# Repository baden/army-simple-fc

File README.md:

## Планую розробити власний контролер автопілота та польотний контролер.

## Розподілення каналів.

Канал | Де на пульті | Призначення
:-----:|:--------:|:------
1 | Ail правий стік вліво-вправо  | Повертання та разворот на місці 
2 | Ele правий стік донизу-догори | Рух вперед-назад
3 | Thr лівий стік донизу-догори  | Керування газом двигуна
4 | Rud лівий стік вліво-вправо   | Не задіян
5 | SA Арм/Дісарм (лівий двохпозиційний стік)  | Дозвіл на керування. При вимиканні зупиняє рух та вимикає двигун
6 | лівий трьохпозиційний стік | Не задіян
7 | правий трьохпозиційний стік | Не задіян
8 | правий двохпозиційний стік | Не задіян
9 | Назначається на нижню кнопку зліва, без фіксації | Глушення мотору, або декомпресор для старту
10 | Назначається на середню кнопку зліва, без фіксації | Стартер
11 | Назначається на верхню кнопку зліва, з фіксацією | Дозвіл на запуск двигуна. Не під'єднан.
12 | Назначається на верхню та нижню кнопки з правої сторони. | Керування лебідкою.
13 |
14 |
15 |
16 |

## Звукові сигнали

При подачі живлення видається короткий звуковий сигнал.
При підключенні до пульта видається другий звуковий сигнал.
При активації ARM видається третій звуковий сигнал.
При диактивації ARM видається два звукових сигнала.
При втачанні звʼязку з пультом видається три звукових сигнала.
При втрачанні звʼязку більше ніж на хвилину, видається три довгих звукових сигнали.

# Нахрін ZephyrOS. Все шо далі не читайте. Може колись повернусь.

# По ПО.

## Налаштування робочого оточення

Я використовую (коли згадую) оце: [uv](https://github.com/astral-sh/uv)
Але зі звичайним python/pip це працює точнісенько так само.

```
uv venv --python 3.12
source .venv/bin/activate
uv pip install west

cd zephyrproject
west init -l army-simple-fc
west update
uv pip install -r zephyr/scripts/requirements.txt
#west config --global zephyr.base-prefer configfile
west zephyr-export
west build -s army-simple-fc -p -b army_simple_fc_v1_0

```

Збірка

```
west build -s army-simple-fc -p -b army_simple_fc_v1_0
```

Це вже не актуально:

```
uv venv --python 3.12
source .venv/bin/activate
uv pip install west
west init -m https://github.com/baden/fxa-custom-zephyr --mr main zephyrproject
cd zephyrproject
west update
west zephyr-export
uv pip install -r zephyr/scripts/requirements.txt
```

Напевно ще треба зробити 

```
cd zephyr
west sdk install
```

але я поки не хочу, бо це довго і багато буде качати

Пробуємо шось зібрати

```
west build -p always -b nucleo_g070rb zephyr/samples/basic/blinky -d build-blinky
```

Сука, воно знов зависає на 

Found GnuLd: /Users/baden/.local/opt/zephyr-sdk-0.16.4/arm-zephyr-eabi/bin/../lib/gcc/arm-zephyr-eabi/12.2.0/../../../../arm-zephyr-eabi/bin/ld.bfd (found version "2.38")

## Подальша інформація не актуальна

Вибір процесору:

STM32F030CCT6TR - LQFP-48 (0.5мм)
https://kosmodrom.ua/mikrokontroler/stm32f030cct6.html
47,5грн

STM32G070CBT6 - LQFP-48 (0.5мм)
https://kosmodrom.ua/mikrokontroler/stm32g070cbt6.html
47,5грн

Якшо треба більш компактну:
STM32G070KBT6 - LQFP-32 (0.8мм) - це буде простіше припаяти.
https://kosmodrom.ua/mikrokontroler/stm32g070kbt6.html

### Різні посилання

- https://habr.com/ru/articles/731514/ - Про керування VTX
- https://www.team-blacksheep.com/media/files/tbs_smartaudio_rev09.pdf
- https://betaflight.com/docs/wiki/guides/current/smartaudio
- https://github.com/EonClaw/STM32F411-Blackpill-INAV-FixedWing
- https://github.com/iNavFlight/OpenTX-Telemetry-Widget
- https://github.com/SolidGeek/VescUart

# army-simple-fc

Тут буде і плата і програма.

## Встановлення інструментів

https://github.com/riscv-software-src/homebrew-riscv

```bash
brew tap riscv-software-src/riscv
brew install riscv-tools
brew install riscv-openocd
brew test riscv-tools
/opt/homebrew/opt/riscv-gnu-toolchain/bin/riscv64-unknown-elf-gcc --version
```

/opt/homebrew/opt/riscv-openocd/bin/openocd

Во, подивиться це:

https://github.com/wagiminator/CH32V003-GameConsole/tree/main

Ще це:
https://github.com/wagiminator/MCU-Templates

Ще тут купа посилань:
https://github.com/wagiminator/Development-Boards/tree/main/CH32V003A4M6_DevBoard

https://github.com/AlessandroAU/ESP32-CRSF-Packet-Gen/blob/master/CRSF_testcode/CRSF.h
https://px4.github.io/Firmware-Doxygen/d9/dd2/crsf_8cpp_source.html

https://github.com/vedderb/bldc_uart_comm_stm32f4_discovery/blob/c19a6283e187040f25aa52e213673938db054d06/bldc_interface.c#L567

https://vedder.se/2015/10/communicating-with-the-vesc-using-uart/

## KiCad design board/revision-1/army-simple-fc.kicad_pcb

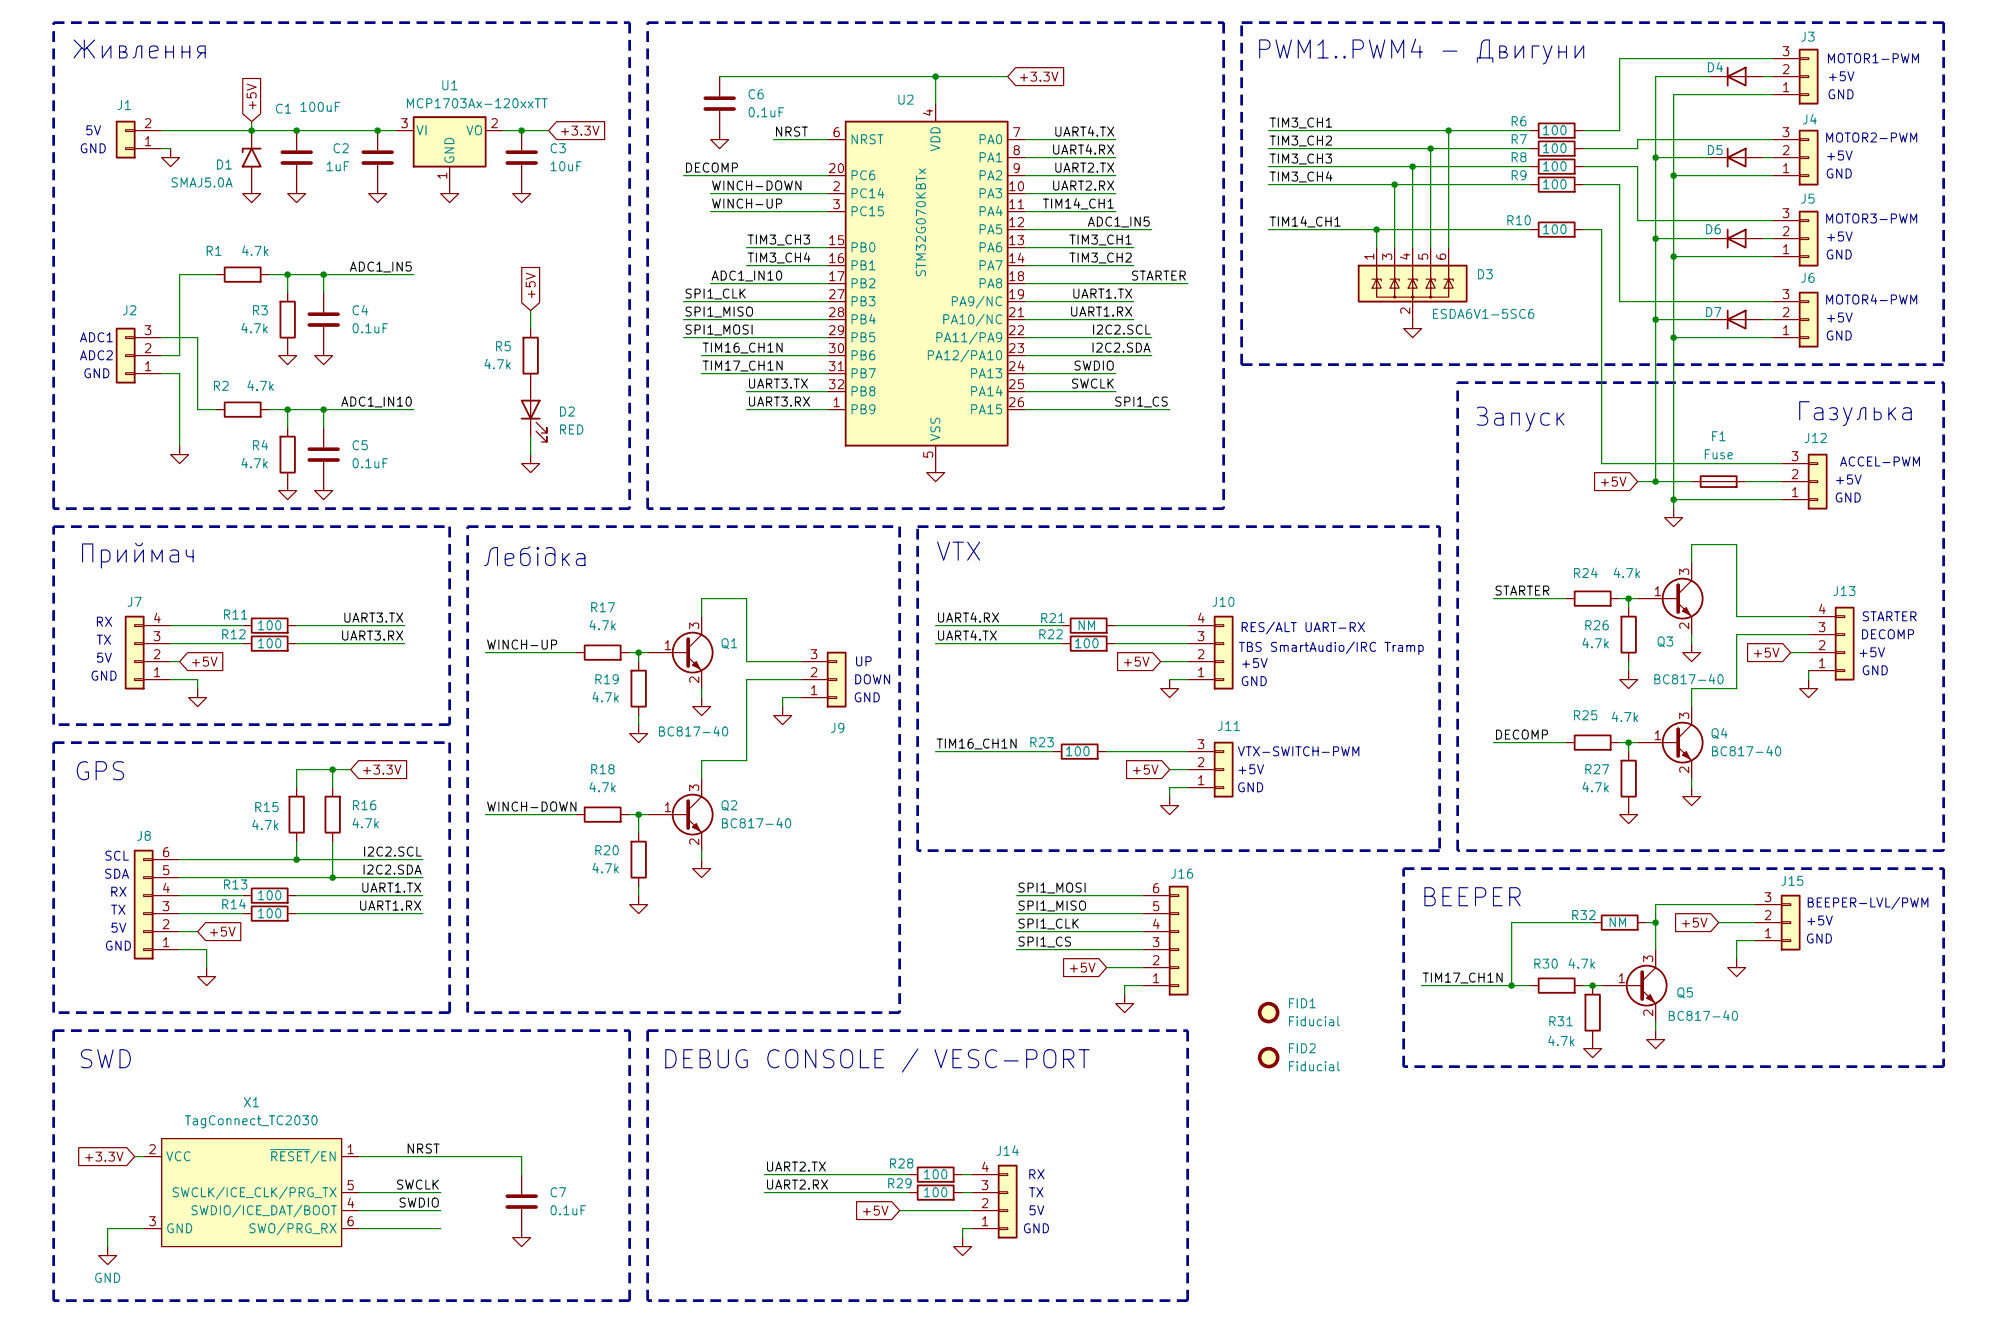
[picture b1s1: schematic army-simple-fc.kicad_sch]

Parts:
C1: 100uF; C_1206_3216Metric
C2: 1uF; C_0603_1608Metric
C3: 10uF; C_0603_1608Metric
C4, C5, C6, C7: 0.1uF; C_0603_1608Metric
D1: SMAJ5.0A; D_SMA
D2: RED; LED_0603_1608Metric
D3: ESDA6V1-5SC6; SOT-23-6
D4, D5, D6, D7: D; D_SOD-123
F1: Fuse; Fuse_1206_3216Metric
FID1, FID2: Fiducial; Fiducial_1mm_Mask2mm
J1: Conn_01x03; JST_PH_B2B-PH-K_1x02_P2.00mm_Vertical
J2, J3, J4, J5, J6, J9, J11, J12, J15: Conn_01x03; JST_PH_B3B-PH-K_1x03_P2.00mm_Vertical
J7, J10, J13, J14: Conn_01x03; JST_PH_B4B-PH-K_1x04_P2.00mm_Vertical
J8, J16: Conn_01x06; JST_PH_B6B-PH-K_1x06_P2.00mm_Vertical
Q1, Q2, Q3, Q4, Q5: BC817-40; SOT-23
R1, R2, R3, R4, R5, R15, R16, R17, R18, R19, R20, R24, R25, R26, R27, R30, R31: 4.7k; R_0603_1608Metric
R6, R7, R8, R9, R10, R11, R12, R13, R14, R22, R23, R28, R29: 100; R_0603_1608Metric
R21, R32: NM; R_0603_1608Metric
U1: MCP1703Ax-120xxTT; SOT-23
U2: STM32G070KBTx; LQFP-32_7x7mm_P0.8mm
X1: TagConnect_TC2030; TC2030-MCP

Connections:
+3.3V: C3.1, C6.1, R15.2, R16.2, U1.2 (VO), U2.4 (VDD), X1.2 (VCC)
+5V: C1.1, C2.1, D1.1 (A1), D4.1 (K), D5.1 (K), D6.1 (K), D7.1 (K), F1.1, J1.2, J7.2, J8.2, J10.2, J11.2, J13.2, J14.2, J15.2, J16.2, R5.2, U1.3 (VI)
/ADC1_IN5: C4.1, R1.2, R3.2, U2.12 (PA5)
/ADC1_IN10: C5.1, R2.2, R4.2, U2.17 (PB2)
/DECOMP: R25.1, U2.20 (PC6)
/I2C2.SCL: J8.6, R15.1, U2.22 (PA11/PA9)
/I2C2.SDA: J8.5, R16.1, U2.23 (PA12/PA10)
/NRST: C7.1, U2.6 (NRST), X1.1 (~RESET/EN)
/SPI1_CLK: J16.4, U2.27 (PB3)
/SPI1_CS: J16.3, U2.26 (PA15)
/SPI1_MISO: J16.5, U2.28 (PB4)
/SPI1_MOSI: J16.6, U2.29 (PB5)
/STARTER: R24.1, U2.18 (PA8)
/SWCLK: U2.25 (PA14), X1.5 (SWCLK/ICE_CLK/PRG_TX)
/SWDIO: U2.24 (PA13), X1.4 (SWDIO/ICE_DAT/BOOT)
/TIM3_CH1: D3.6 (IO5), R6.1, U2.13 (PA6)
/TIM3_CH2: D3.5 (IO4), R7.1, U2.14 (PA7)
/TIM3_CH3: D3.4 (IO3), R8.1, U2.15 (PB0)
/TIM3_CH4: D3.3 (IO2), R9.1, U2.16 (PB1)
/TIM14_CH1: D3.1 (IO1), R10.1, U2.11 (PA4)
/TIM16_CH1N: R23.1, U2.30 (PB6)
/TIM17_CH1N: R30.1, R32.1, U2.31 (PB7)
/UART1.RX: R14.2, U2.21 (PA10/NC)
/UART1.TX: R13.2, U2.19 (PA9/NC)
/UART2.RX: R29.1, U2.10 (PA3)
/UART2.TX: R28.1, U2.9 (PA2)
/UART3.RX: R12.2, U2.1 (PB9)
/UART3.TX: R11.2, U2.32 (PB8)
/UART4.RX: R21.1, U2.8 (PA1)
/UART4.TX: R22.1, U2.7 (PA0)
/WINCH-DOWN: R18.1, U2.2 (PC14)
/WINCH-UP: R17.1, U2.3 (PC15)
GND: C1.2, C2.2, C3.2, C4.2, C5.2, C6.2, C7.2, D1.2 (A2), D2.1 (K), D3.2 (GND), J1.1, J2.1, J3.1, J4.1, J5.1, J6.1, J7.1, J8.1, J9.1, J10.1, J11.1, J12.1, J13.1, J14.1, J15.1, J16.1, Q1.2 (E), Q2.2 (E), Q3.2 (E), Q4.2 (E), Q5.2 (E), R3.1, R4.1, R19.1, R20.1, R26.1, R27.1, R31.1, U1.1 (GND), U2.5 (VSS), X1.3 (GND)
unnamed: D2.2 (A), R5.1
unnamed: D4.2 (A), J3.2
unnamed: D5.2 (A), J4.2
unnamed: D6.2 (A), J5.2
unnamed: D7.2 (A), J6.2
unnamed: J2.2, R1.1
unnamed: J2.3, R2.1
unnamed: J3.3, R6.2
unnamed: J4.3, R7.2
unnamed: J5.3, R8.2
unnamed: J6.3, R9.2
unnamed: J7.3, R12.1
unnamed: J7.4, R11.1
unnamed: J8.3, R14.1
unnamed: J8.4, R13.1
unnamed: J9.2, Q2.3 (C)
unnamed: J9.3, Q1.3 (C)
unnamed: J10.3, R22.2
unnamed: J10.4, R21.2
unnamed: J11.3, R23.2
unnamed: F1.2, J12.2
unnamed: J12.3, R10.2
unnamed: J13.3, Q4.3 (C)
unnamed: J13.4, Q3.3 (C)
unnamed: J14.3, R29.2
unnamed: J14.4, R28.2
unnamed: J15.3, Q5.3 (C), R32.2
unnamed: Q1.1 (B), R17.2, R19.2
unnamed: Q2.1 (B), R18.2, R20.2
unnamed: Q3.1 (B), R24.2, R26.2
unnamed: Q4.1 (B), R25.2, R27.2
unnamed: Q5.1 (B), R30.2, R31.2

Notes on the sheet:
PWM1..PWM4 - Двигуни
ADC1
+5V
ACCEL-PWM
GND
Лебідка
ADC2
BEEPER
SWD
VTX-SWITCH-PWM
Приймач
VTX
DOWN
RES/ALT UART-RX
Запуск
BEEPER-LVL/PWM
GPS
DEBUG CONSOLE / VESC-PORT
SDA
Газулька
DECOMP
MOTOR2-PWM
MOTOR3-PWM
MOTOR1-PWM
STARTER
Живлення
MOTOR4-PWM
TBS SmartAudio/IRC Tramp
SCL

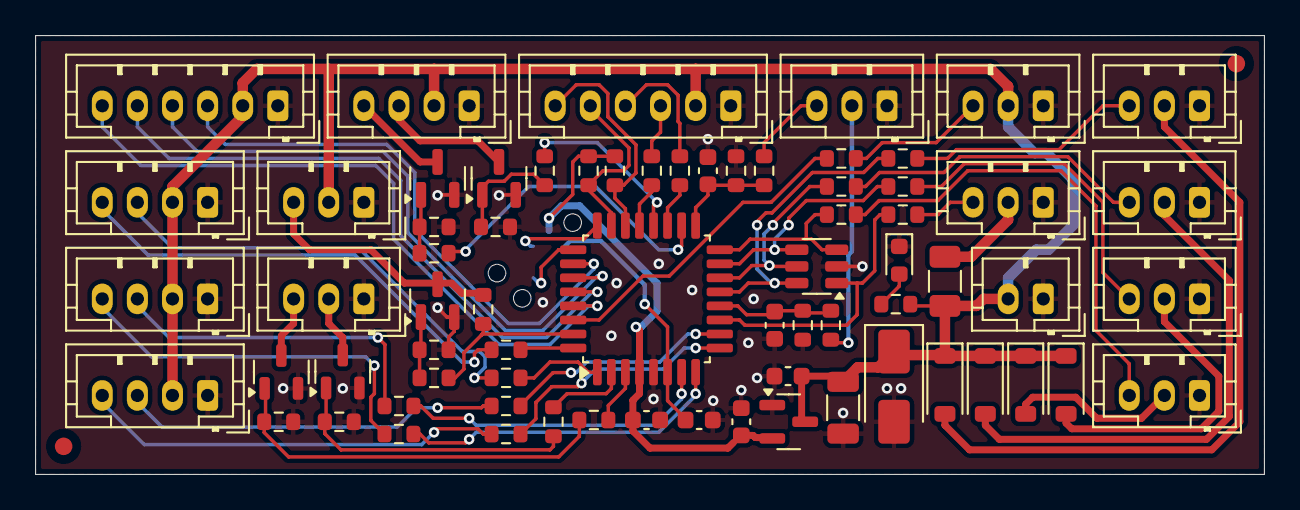
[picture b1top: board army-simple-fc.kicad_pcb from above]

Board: 2 copper layers, 70.0 x 25.0 mm, 73 parts (1 on the bottom side), 65 nets.

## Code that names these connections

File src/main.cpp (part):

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// https://docs.arduino.cc/libraries/alfredocrsf/#Releases

// Motor servos pins
constexpr int moto1_servo_pin = PA6;
constexpr int moto2_servo_pin = PA7;
constexpr int moto3_servo_pin = PB0;
constexpr int moto4_servo_pin = PB1;

// ADC pins (inpu1-in5/PA5, input2-in10/PB2)
constexpr int adc1_pin = PA5;
constexpr int adc2_pin = PB2;

// Winch direction pins
constexpr int winch_up_pin = PC15;
constexpr int winch_down_pin = PC14;

// Start/stop digital pins
constexpr int starter_pin = PA8;
constexpr int decompressor_pin = PC6;
// Acceleration servo pin
constexpr int acc_servo_pin = PA4;

// Beeper digital pin
constexpr int beeper_pin = PB7;


// TODO: GPS UART & I2C
constexpr int gps_i2c_sda_pin = PA12;
constexpr int gps_i2c_scl_pin = PA11;


// Motor servos
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    digitalWrite(winch_down_pin, LOW);

    // Init Start/stop pins
    pinMode(starter_pin, OUTPUT);
    digitalWrite(starter_pin, LOW);
    pinMode(decompressor_pin, OUTPUT);
    digitalWrite(decompressor_pin, LOW);
    // Acceleration servo pin
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            int starter_value = crsf.getChannel(10);
            if(starter_value > 1500) {
                if(armed) {
                    digitalWrite(starter_pin, HIGH);
                } else {
                    digitalWrite(starter_pin, LOW);
                }
            } else {
                digitalWrite(starter_pin, LOW);
            }

            // Канал 9 - Вихід декомпресора
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                    beeper_short_signals(3);

                }
                digitalWrite(starter_pin, LOW);
                digitalWrite(decompressor_pin, LOW);
                digitalWrite(winch_up_pin, LOW);
                digitalWrite(winch_down_pin, LOW);
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
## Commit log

2024-10-10 Трохи накидав.
2024-10-11 Майже всунув.
2024-10-11 Майже закінчив.
2024-10-11 Завершив. Почнемо збирати гербери.
2024-10-11 Сгенеровані гербери.
2024-10-15 Все. Теперь точно.
2024-11-08 Шось з Zephyr-project не зростається.
2024-11-08 Нахрін зефір, робимо на ардуіно.
2024-11-08 Цей platformio теж мене трохи напружує.
2024-11-10 Якось працює.
2024-11-10 Ой, попередній коміт не все додав.
2024-11-11 Змінені звукові сигнали. Збільшен буфер RX UART.
2024-11-11 Все, можна прошивати та тестувати.
2024-11-11 Значно зменшив затримку після ініціалізації шоб запобігти переповненню буферу UART.
2024-11-11 В процедурі зупинки по таймауту функції затримки замінени на неблокуючи.
2024-11-28 Двигуни тепер мають ШІМ 1000...2000.
2024-11-28 Додані хекси.
